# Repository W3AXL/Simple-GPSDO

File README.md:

# Simple GPSDO
 a derivative of Lar's Arduino GPSDO with some added spice

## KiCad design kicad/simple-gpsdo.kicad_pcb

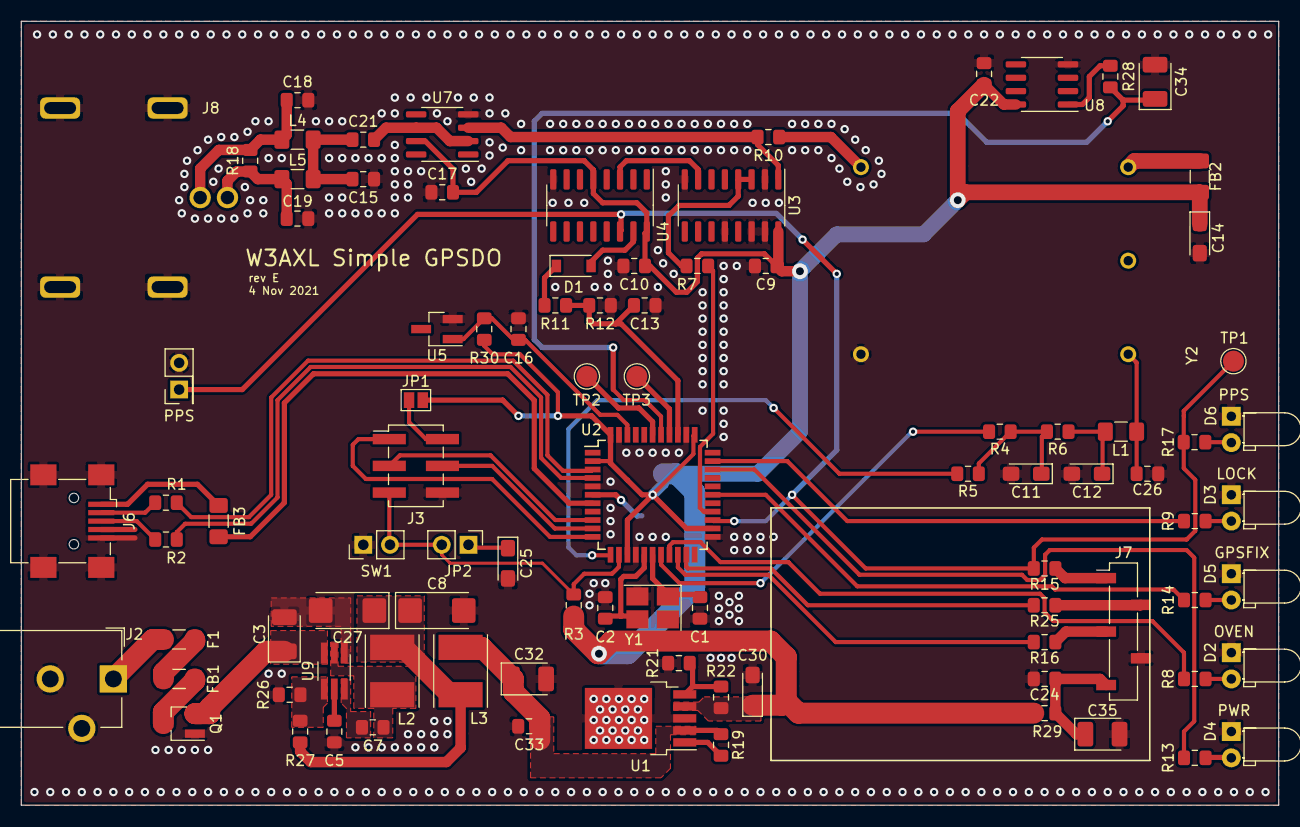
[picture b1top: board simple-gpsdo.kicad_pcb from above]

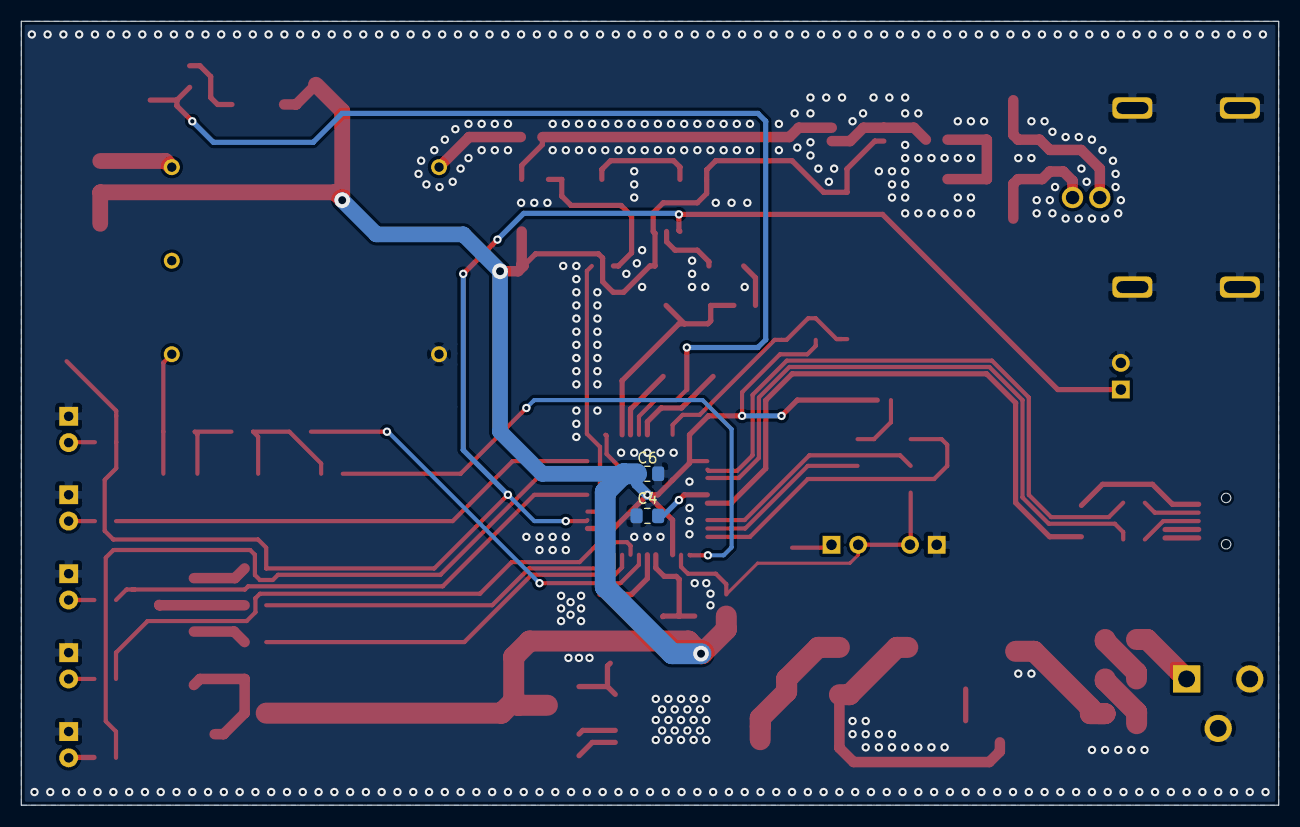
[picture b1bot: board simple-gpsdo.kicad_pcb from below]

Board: 2 copper layers, 119.5 x 74.5 mm, 95 parts (2 on the bottom side), 68 nets.

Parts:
C1, C2: 6.8pF; C_0805_2012Metric_Pad1.15x1.40mm_HandSolder
C3, C32, C34, C35: 10uF; CP_EIA-3528-15_AVX-H_Pad1.50x2.35mm_HandSolder
C4: 1uF; C_0805_2012Metric_Pad1.15x1.40mm_HandSolder
C5, C13: 1nF; C_0805_2012Metric_Pad1.15x1.40mm_HandSolder
C6, C7, C9, C10, C16, C17, C21, C22, C24, C26, C33: 0.1uF; C_0805_2012Metric_Pad1.15x1.40mm_HandSolder
C8, C27: 22uF; CP_EIA-6032-20_AVX-F_Pad2.25x2.35mm_HandSolder
C11, C12, C14, C25, C30: 4.7uF; CP_EIA-3216-10_Kemet-I_Pad1.58x1.35mm_HandSolder
C15, C18, C19: 330pF; C_0805_2012Metric_Pad1.15x1.40mm_HandSolder
D1: 1N6263; D_SOD-123
D2: OVEN; LED_D3.0mm_Horizontal_O1.27mm_Z2.0mm
D3: TLOCK; LED_D3.0mm_Horizontal_O1.27mm_Z2.0mm
D4: POWER; LED_D3.0mm_Horizontal_O1.27mm_Z2.0mm
D5: GLOCK; LED_D3.0mm_Horizontal_O1.27mm_Z2.0mm
D6: PPS; LED_D3.0mm_Horizontal_O1.27mm_Z2.0mm
F1: 2A; Fuse_1206_3216Metric_Pad1.42x1.75mm_HandSolder
FB1, FB2, FB3: Ferrite; Fuse_1206_3216Metric_Pad1.42x1.75mm_HandSolder
J1: PPS_OUT; PinHeader_2x01_P2.54mm_Vertical
J2: PWR; BarrelJack_CUI_PJ-102AH_Horizontal
J3: ISP; PinHeader_2x03_P2.54mm_Vertical_SMD
J6: USB_B_Micro; USB_Mini-B_Wuerth_65100516121_Horizontal
J7: NEO-6M; PinSocket_1x05_P2.54mm_Vertical_SMD_Pin1Left
J8: 10MHz_OUT; 734152980
JP1: ISP_VCC; SolderJumper-2_P1.3mm_Open_Pad1.0x1.5mm
JP2: RST_BP; PinHeader_1x02_P2.54mm_Vertical
L1: 3.3uH; L_1206_3216Metric_Pad1.42x1.75mm_HandSolder
L2, L3: 3.3uH; L_Taiyo-Yuden_NR-50xx_HandSoldering
L4, L5: 1uH; L_1206_3216Metric_Pad1.42x1.75mm_HandSolder
Q1: PJA3407; SOT-23_Handsoldering
R1, R2: 22R; R_0805_2012Metric_Pad1.15x1.40mm_HandSolder
R3, R19, R21, R26: 10k; R_0805_2012Metric_Pad1.15x1.40mm_HandSolder
R4, R6: 39k; R_0805_2012Metric_Pad1.15x1.40mm_HandSolder
R5, R12: 10M; R_0805_2012Metric_Pad1.15x1.40mm_HandSolder
R7, R10, R15, R16, R18, R25: 100; R_0805_2012Metric_Pad1.15x1.40mm_HandSolder
R8, R9, R13, R14, R17: 470; R_0805_2012Metric_Pad1.15x1.40mm_HandSolder
R11, R30: 3k9; R_0805_2012Metric_Pad1.15x1.40mm_HandSolder
R22, R27: 65k; R_0805_2012Metric_Pad1.15x1.40mm_HandSolder
R28: 68R; R_0805_2012Metric_Pad1.15x1.40mm_HandSolder
R29: 2R; R_0805_2012Metric_Pad1.15x1.40mm_HandSolder
SW1: RST; PinHeader_1x02_P2.54mm_Vertical
TP1: PPS; TestPoint_Pad_D2.0mm
TP2: ADC3; TestPoint_Pad_D2.0mm
TP3: ADC1; TestPoint_Pad_D2.0mm
U1: XRP6272ITC5TR-F; TO-252-5_TabPin3
U2: ATmega32U4-AU; TQFP-44_10x10mm_P0.8mm
U3: MC74HC390; SOIC-16_3.9x9.9mm_P1.27mm
U4: CD74HC4046AM96; SOIC-16_3.9x9.9mm_P1.27mm
U5: LM4041DFTA; SOT-23_Handsoldering
U7: TLV3541IDR; SOIC-8_3.9x4.9mm_P1.27mm
U8: LM35-D; SOIC-8_3.9x4.9mm_P1.27mm
U9: AP62150WU-7; TSOT-23-6_HandSoldering
Y1: 16MHz; Crystal_SMD_SeikoEpson_TSX3225-4Pin_3.2x2.5mm_HandSoldering
Y2: NV47X; CO-08

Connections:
5MHz: R7.1, U2.26
10MHz: R10.1, U3.1, U7.3
+5V: C6.2, C9.2, C10.2, C14.1, C17.2, C22.2, C30.1, FB2.1, JP1.2, R3.1, R22.2, R29.1, R30.1, U1.4, U2.2, U2.14, U2.24, U2.34, U2.44, U3.16, U4.5, U4.16, U7.7, U8.8
+6V: C32.1, C33.1, L3.2, R19.1, U1.2
/1MHz: U3.7, U4.3
/ADC2: C34.1, R28.1, U2.38
/PWM_D3: R4.2, U2.18
/PWM_D11: R5.2, U2.12
ADC0: C13.2, R11.2, R12.1, U2.36
GND: C1.1, C2.1, C3.2, C4.1, C5.1, C6.1, C8.2, C9.1, C10.1, C11.2, C12.2, C13.1, C14.2, C15.1, C16.1, C17.1, C18.1, C19.2, C22.1, C24.1, C25.2, C26.1, C27.2, C30.2, C32.2, C33.2, C34.2, C35.2, D2.1, D3.1, D4.1, D5.1, D6.1, J1.2, J2.2, J2.3, J3.6, J6.5, J6.6, J7.4, J8.3, Q1.1, R12.2, R21.2, R26.2, SW1.1, U1.3, U2.5, U2.15, U2.23, U2.35, U2.43, U3.2, U3.8, U3.12, U3.14, U3.15, U4.8, U5.2, U7.4, U8.4, U9.1, Y1.2, Y1.4, Y2.5
GPS_LOCK: R14.2, U2.28
GPS_PPS: J1.1, R15.1, R17.2, TP1.1, U2.25, U4.14
GPS_RX: R25.1, U2.21
GPS_TX: R16.1, U2.20
ISP_MISO: J3.1, U2.11
ISP_MOSI: J3.4, U2.10
ISP_SCK: J3.3, U2.9
unnamed: C3.1, Q1.2, U9.3
unnamed: C4.2, U2.6
unnamed: C5.2, U9.5
unnamed: C7.1, U9.6
unnamed: C7.2, L2.1, U9.2
unnamed: C11.1, R4.1, R5.1, R6.2
unnamed: C15.2, C21.1, L4.2, L5.2
unnamed: C16.2, R30.2, U2.42, U5.1
unnamed: C18.2, J8.2, L4.1, R18.2
unnamed: C19.1, J8.1, L5.1, R18.1
unnamed: C21.2, U7.2, U7.6
unnamed: C24.2, C35.1, J7.5, R29.2
unnamed: C25.1, JP2.1
unnamed: C26.2, L1.2, Y2.1
unnamed: C8.1, C27.1, L2.2, L3.1, R27.2
unnamed: D1.1, R11.1
unnamed: D1.2, U4.15
unnamed: D2.2, R8.1
unnamed: D3.2, R9.1
unnamed: D4.2, R13.1
unnamed: D5.2, R14.1
unnamed: D6.2, R17.1
unnamed: F1.1, FB1.1
unnamed: F1.2, J2.1
unnamed: FB1.2, Q1.3
unnamed: FB2.2, Y2.3
unnamed: FB3.1, J6.1
unnamed: FB3.2, U2.7
unnamed: J3.2, JP1.1
unnamed: J6.2, R1.2
unnamed: J6.3, R2.1
unnamed: J7.1, R15.2
unnamed: J7.2, R25.2
unnamed: J7.3, R16.2
unnamed: R1.1, U2.3
unnamed: R2.2, U2.4
unnamed: R7.2, U3.3, U3.4
unnamed: R10.2, Y2.4
unnamed: R19.2, U1.1
unnamed: R21.1, R22.1, U1.5
unnamed: R26.1, R27.1, U9.4
unnamed: R28.2, U8.1
unnamed: TP2.1, U2.39
unnamed: TP3.1, U2.37
OSC_CTRL: C12.1, L1.1, R6.1
OVEN_TEMP: R8.2, U2.19
POWER_OK: R13.2, U2.31
TIME_LOCK: R9.2, U2.32
XTAL1: C1.2, U2.17, Y1.1
XTAL2: C2.2, U2.16, Y1.3
~RST: J3.5, JP2.2, R3.2, SW1.2, U2.13

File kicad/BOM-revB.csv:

Ref,Qnty,Value,Cmp name,Footprint,Description,Vendor
"C1, C2, ",2,6.8pF,C_Small,Capacitor_SMD:C_0805_2012Metric_Pad1.15x1.40mm_HandSolder,"Unpolarized capacitor, small symbol",
"C3, C5, ",2,0.33uF,C_Small,,"Unpolarized capacitor, small symbol",
"C4, ",1,1uF,C_Small,,"Unpolarized capacitor, small symbol",
"C6, C7, C8, C9, C10, C14, C15, C16, C17, C18, C19, C20, C21, C22, C23, C24, C26, ",17,0.1uF,C_Small,,"Unpolarized capacitor, small symbol",
"C11, C12, C25, ",3,4.7uF,CP_Small,,"Polarized capacitor, small symbol",
"C13, ",1,1nF,C_Small,,"Unpolarized capacitor, small symbol",
"D1, ",1,1N5711,D_Schottky_Small,,"Schottky diode, small symbol",
"D2, ",1,OVEN,LED,,Light emitting diode,
"D3, ",1,TLOCK,LED,,Light emitting diode,
"D4, ",1,POWER,LED,,Light emitting diode,
"D5, ",1,GLOCK,LED,,Light emitting diode,
"F1, ",1,2A,Polyfuse_Small,,"Resettable fuse, polymeric positive temperature coefficient, small symbol",
"FB1, FB2, ",2,Ferrite,Ferrite_Bead_Small,,"Ferrite bead, small symbol",
"J1, ",1,USB_B_Mini,USB_B_Mini,,USB Mini Type B connector,
"J2, ",1,Barrel_Jack_Switch,Barrel_Jack_Switch,,DC Barrel Jack with an internal switch,
"J3, ",1,AVR-ISP-6,AVR-ISP-6-Connector,,,
"J4, ",1,GPS_NEO,Conn_Coaxial,,"coaxial connector (BNC, SMA, SMB, SMC, Cinch/RCA, ...)",
"J5, ",1,GPS_IN,Conn_Coaxial,,"coaxial connector (BNC, SMA, SMB, SMC, Cinch/RCA, ...)",
"J6, J8, ",2,10MHz_OUT,Conn_Coaxial_x2,,"double coaxial connector (BNC, SMA, SMB, SMC, Cinch/RCA, ...)",
"J7, ",1,NEO-6M,Conn_01x05_Female,,"Generic connector, single row, 01x05, script generated (kicad-library-utils/schlib/autogen/connector/)",
"JP1, ",1,ISP_VCC,Jumper_NO_Small,,"Jumper, normally open, small symbol",
"JP2, ",1,RST_BP,Jumper_NC_Small,,"Jumper, normally closed, small symbol",
"L1, ",1,33uH,L_Small,,"Inductor, small symbol",
"R1, R2, ",2,22R,R_Small,,"Resistor, small symbol",
"R3, R17, R18, R19, R20, ",5,10k,R_Small,,"Resistor, small symbol",
"R4, R6, ",2,39k,R_Small,,"Resistor, small symbol",
"R5, R12, ",2,10M,R_Small,,"Resistor, small symbol",
"R7, R10, R15, R16, R25, ",5,100,R_Small,,"Resistor, small symbol",
"R8, R9, R13, R14, ",4,470,R_Small,,"Resistor, small symbol",
"R11, ",1,3k9,R_Small,,"Resistor, small symbol",
"R21, R22, R23, R24, ",4,50R,R_Small,,"Resistor, small symbol",
"SW1, ",1,RST,SW_Push,,"Push button switch, generic, two pins",
"TP1, ",1,PPS,TestPoint,,test point,
"TP2, ",1,ADC3,TestPoint,,test point,
"TP3, ",1,ADC1,TestPoint,,test point,
"U1, U5, ",2,AS7805,L7805,,"Positive 1.5A 35V Linear Regulator, Fixed Output 5V, TO-220/TO-263/TO-252",
"U2, ",1,ATmega32U4-AU,ATmega32U4-AU-MCU_Microchip_ATmega,Package_QFP:TQFP-44_10x10mm_P0.8mm,,
"U3, ",1,MC74HC390,MC74HC390,,,
"U4, ",1,CD74HC4046AM96,CD74HC4046AM96,,,
"U6, U7, ",2,LM7171,AD8610,,"Single Precision, Very Low Noise, Low Input Bias Current, Wide Bandwidth JFET Operational Amplifiers, SOIC-8",
"U8, ",1,LM35-D,LM35-D,Package_SO:SOIC-8_3.9x4.9mm_P1.27mm,"Precision centigrade temperature sensor, SOIC-8",
"Y1, ",1,16MHz,Crystal_Small,,"Two pin crystal, small symbol",
"Y2, ",1,NV47X,NV47X,,,

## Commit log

2020-09-15 initial github commit
    kicad schematic WIP
2020-09-17 kicad schematic work
2020-09-17 added 74HCxx symbols
2020-09-17 changed efc control method of OCXO
2020-09-19 finished schematic, started PCB
2020-09-19 finished initial schematic and PCB
2020-09-19 cad stuff
2020-09-19 added renders
2020-09-19 more media
2020-09-19 small images
2020-09-20 images and things
2020-09-20 smaller image
2020-09-21 major schematic change, PCB not yet updated
2020-09-21 more work on updated Rev B schematic/pcb
2020-09-22 more PCB work (still not done)
2020-09-23 more pcb work
2020-09-23 pcb work is hard
2020-09-24 changed regulator setup, way more board work
2020-09-24 new revision, new BOM
2020-09-24 finalizing PCB, added 3D models
2020-09-24 finalizing rev C PCB
2020-09-24 finalizing schematic
2020-09-24 Update sym-lib-table
2020-09-24 initial work on schematic updates
2020-09-25 added extra buck filtering
2020-09-25 finalizing revC schematic and board
2020-09-25 final board and sch exports
2020-09-25 added resistor/cap to NEO power in sch
2020-09-25 added filtering to LM35
2020-09-30 added fan control to schematic, board work still needed
2020-10-16 finalizing revC updates
2020-10-16 updated BOM with new components
2020-10-16 updated board with silkscreen logo and text
2020-10-16 updated pictures, moved BNC jacks slightly inward
2021-04-06 schematic cleanup and re-plot of gerber files
2021-10-22 cleaned up schematic and replaced AP63203 with AP62201
2021-10-22 Revert "cleaned up schematic and replaced AP63203 with AP62201"
    This reverts commit 2d2100cbd1b700602c63588ffeb895ea7c004985.
2021-10-22 replaced excel BOM with CSV
2021-10-22 finalized simple schematic, started PCB rework
2021-10-22 finalized new schematic and board
2021-10-22 Updated tantalum footprints, started new BOM
2021-10-22 Changed 1N5711 to 1N6263 for availability
2021-10-22 Replaced C23 (0.1uF) with C14 (4.7uF)
2021-10-22 Updated LEDs to proper right angle THT, including 3D models
2021-10-22 Changed input fuse from 3A to 2A
2021-10-22 Changed input fuse from 3A to 2A (2/2)
2021-10-23 finalized rev D schematic
2021-10-23 updated board model and photo for rev D
2021-10-23 finalized schematic and PCB
2021-11-03 started firmware
2021-11-03 added new front & rear enclosure panels
2021-11-03 started work on firmware, added needed changes document
2021-11-04 updated schematic with new pin assignment fixes
2021-11-04 more work on code, added combined pdf
2021-11-04 revision E updates
    added external 1.2 VREF
    connected UVCC to VCC
    switched pins for 5MHz, PPS, and LEDs to work properly
2021-11-04 Using external bodged 1.2V-ish VREF in code
2021-11-04 code cleanup, more functions and comments
2021-11-04 Updates to output amplifier, added simulation
2021-11-05 final schematic updates for new buffer amplifier
2021-11-05 amplifier sim
2021-11-05 added status LED routine to code
2021-11-05 more simulation stuff, changed output filter
2021-11-07 finalized output amplifier design
    added wilkinson divider for dual outputs to improve isolation and amplitude
2021-11-07 more schematic and pcb updates
    finished 10MHz output and fixed LED orientation
2021-11-07 schematic for rev E finalized
2021-11-08 Added basic NMEA logging to firmware
    serial log now shows # of sats tracked and HDOP
2021-11-09 added more fault information in serial console and LEDs
2021-11-10 added front panel cutouts svg for laser cutting
2021-11-11 updated LED handling
2021-11-11 lengthened pcb by 0.5mm
2021-12-07 Updated NMEA parser to handle both GPGGA and GNGGA messages
    also added parser for UTC/Z time
2021-12-07 updated to NMEA parsing and printing
    changed order of value prints, and added parser for GPS time
2021-12-08 added parsing for NMEA time & date from ublox module
2021-12-12 Added serial checks to prevent lockup without serial connected
2022-11-28 small changes to kicad schematic and FW
2023-10-30 created updated kicad 7 project and reworking architecture
2023-11-01 more work on schematic
2026-06-05 updated firmware, started work on NMEA parser
